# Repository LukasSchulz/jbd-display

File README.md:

# lifepo4-display

## ToDo:
- B and GND Pins on the rs485-uart/ttl-chip are wrong and need to be switched.
- holes for the screen are to small
- screw of the oled-screen is under the esp-32 

Shield: [![CC BY-NC-SA 4.0][cc-by-nc-sa-shield]][cc-by-nc-sa]

This work is licensed under a
[Creative Commons Attribution-NonCommercial-ShareAlike 4.0 International License][cc-by-nc-sa].

[![CC BY-NC-SA 4.0][cc-by-nc-sa-image]][cc-by-nc-sa]

[cc-by-nc-sa]: http://creativecommons.org/licenses/by-nc-sa/4.0/
[cc-by-nc-sa-image]: https://licensebuttons.net/l/by-nc-sa/4.0/88x31.png
[cc-by-nc-sa-shield]: https://img.shields.io/badge/License-CC%20BY--NC--SA%204.0-lightgrey.svg

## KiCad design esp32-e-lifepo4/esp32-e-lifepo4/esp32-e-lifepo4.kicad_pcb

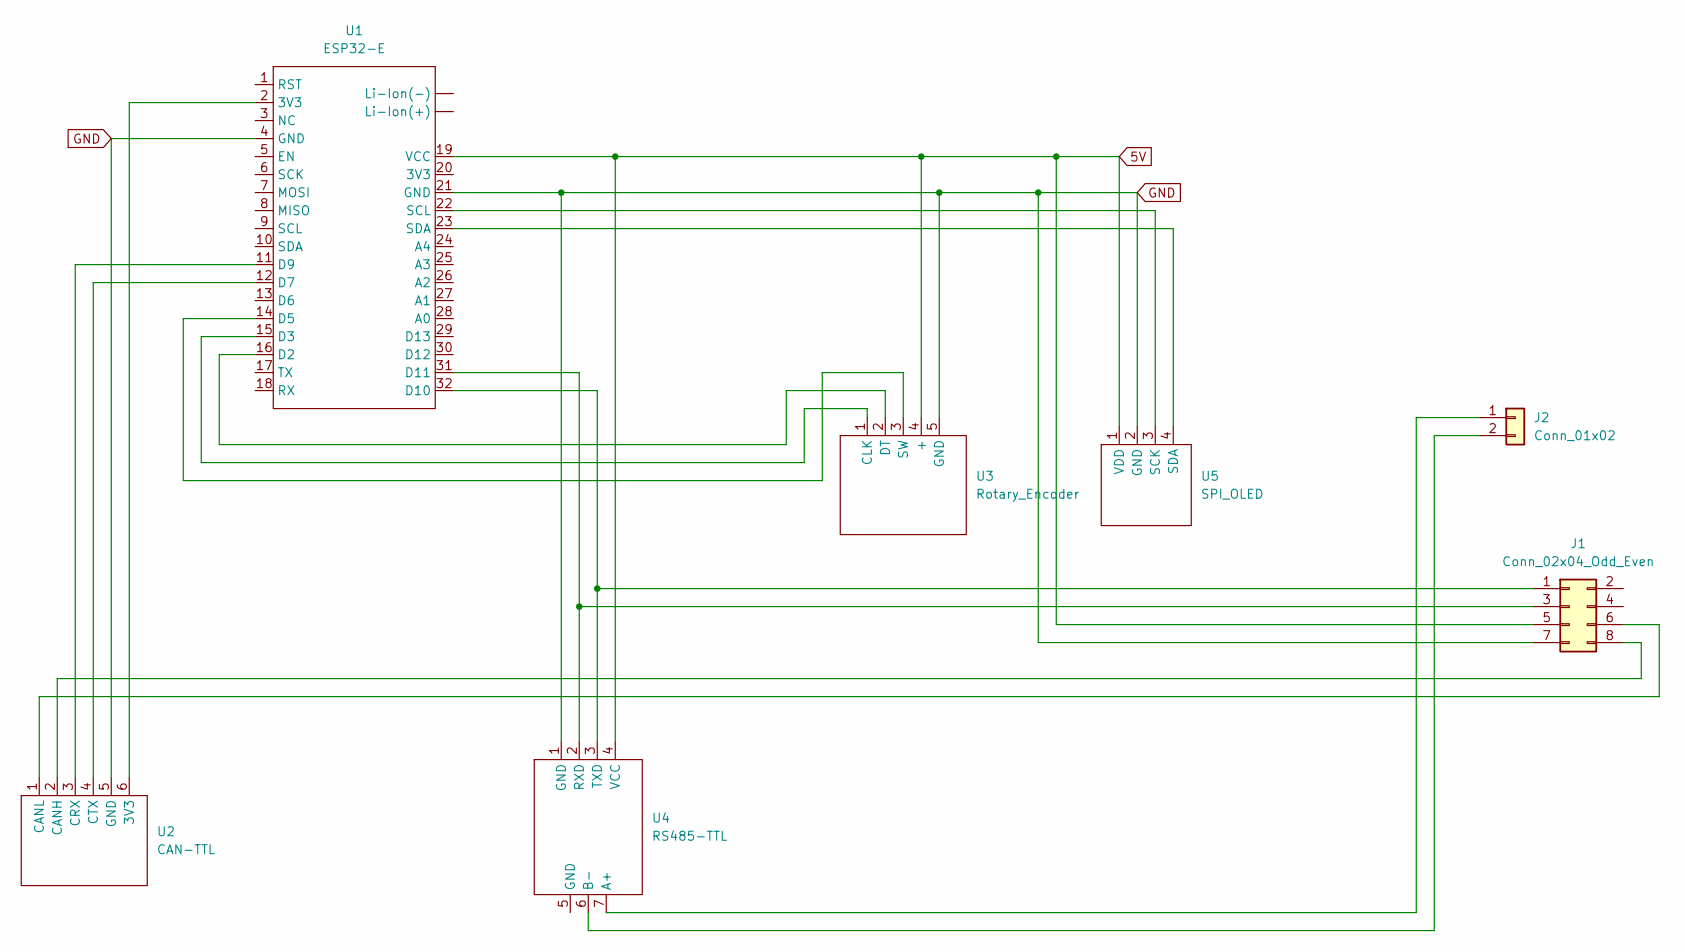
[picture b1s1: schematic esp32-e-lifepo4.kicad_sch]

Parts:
J1: Conn_02x04_Odd_Even; IDC-Header_2x04_P2.54mm_Vertical
J2: Conn_01x02; PinHeader_1x02_P1.00mm_Vertical
U1: ESP32-E
U2: CAN-TTL
U3: Rotary_Encoder
U4: RS485-TTL
U5: SPI_OLED

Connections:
5V: J1.5, U1.19 (VCC), U3.4 (+), U4.4 (VCC), U5.1 (VDD)
GND: J1.7, U1.4 (GND), U1.21 (GND), U2.5 (GND), U3.5 (GND), U4.1 (GND), U5.2 (GND)
unnamed: J1.1, U1.32 (D10), U4.3 (TXD)
unnamed: J1.3, U1.31 (D11), U4.2 (RXD)
unnamed: U1.14 (D5), U3.3 (SW)
unnamed: U1.15 (D3), U3.1 (CLK)
unnamed: U1.16 (D2), U3.2 (DT)
unnamed: U1.22 (SCL), U5.3 (SCK)
unnamed: U1.23 (SDA), U5.4 (SDA)
unnamed: J1.6, U2.1 (CANL)
unnamed: J1.8, U2.2 (CANH)
unnamed: U1.11 (D9), U2.3 (CRX)
unnamed: U1.12 (D7), U2.4 (CTX)
unnamed: U1.2 (3V3), U2.6 (3V3)
unnamed: J2.2, U4.6 (B-)
unnamed: J2.1, U4.7 (A+)

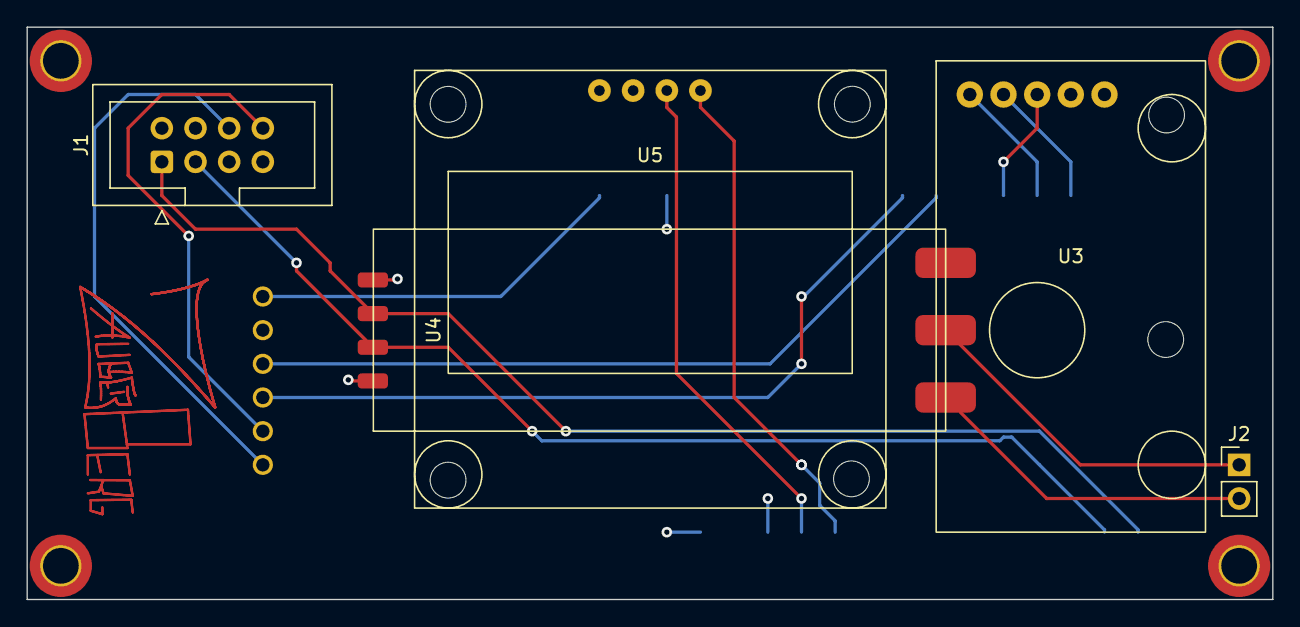
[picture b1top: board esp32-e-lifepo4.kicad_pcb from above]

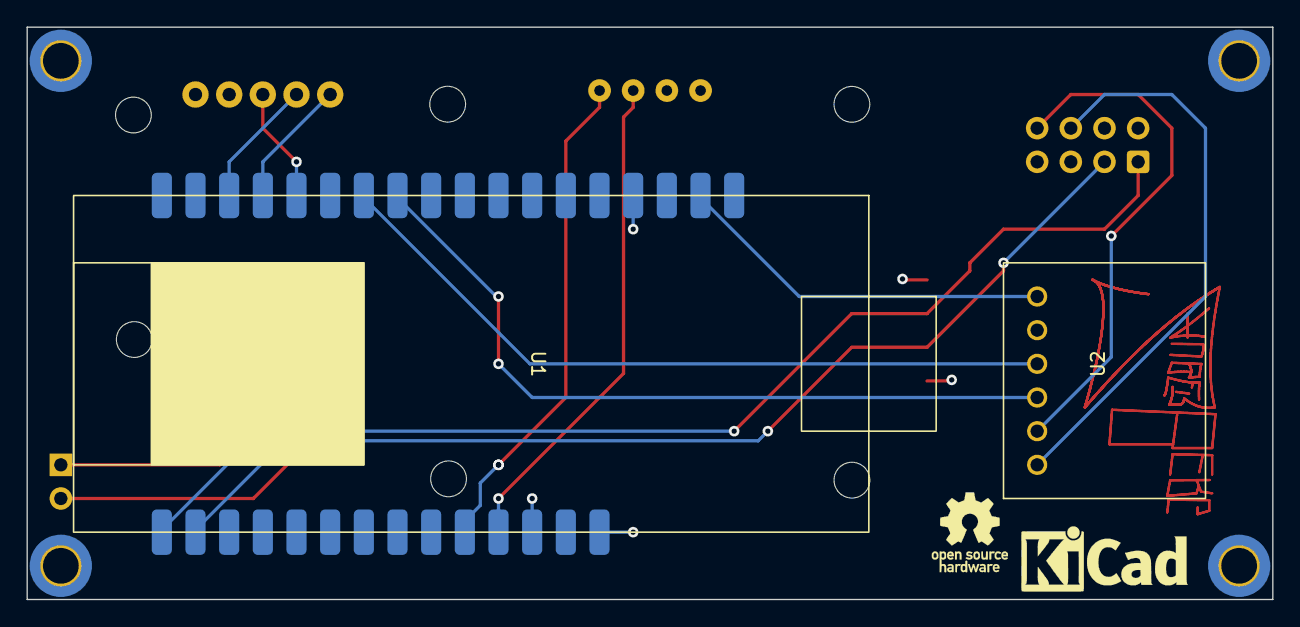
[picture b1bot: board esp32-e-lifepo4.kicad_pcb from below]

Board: 4 copper layers, 94.0 x 43.2 mm, 7 parts (2 on the bottom side), 16 nets.

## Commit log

2023-01-08 Added document for Protocol
2023-01-08 added todo
2023-01-08 updated license
